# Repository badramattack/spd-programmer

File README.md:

# SPD programmer board

A small board to read, edit, program and restore the SPD EEPROM of **DDR4 and
DDR5 DIMMs** (UDIMM and RDIMM), built around a Raspberry Pi Pico (RP2040) and
half of a cut DDR5 DIMM socket. Edits can be made from a PC (`spdtool`) or
with no PC at all: insert a module, hold **Program**, and the board applies a
preset (by default a BadRAM-style extra row address bit) while keeping a
backup; **Restore** undoes it.

- DDR4 (EE1004 + TSE2004) and DDR5 (SPD5118 hub) on one half socket.
- Reversible write protection: DDR4 with the SA0 high voltage generated on the
  board, DDR5 through the hub's offline mode.
- Safety: rails are only on during an operation, after the mode switches and a
  seating check; current-limited supplies; watchdog.
- Decoding and editing of speed, timings, refresh, capacity and identity
  fields; CRCs and the serial number are updated automatically.
- Presets for the Program button are written in Python and uploaded over USB.

| Path | Contents |
|---|---|
| [`kicad/`](kicad/) | KiCad 10 project: schematic, PCB, project footprints (`spd-programmer.pretty`), JLCPCB BOM and placement files, Gerbers |
| [`firmware/`](firmware/) | Pico SDK firmware: USB command interface, buttons, presets ([README](firmware/README.md)) |
| [`host/`](host/) | `spdtool`, the Python host tool and library ([README](host/README.md)) |
| [`docs/`](docs/) | Reference documentation: [hardware](docs/hardware.md), [Program/Restore design and formats](docs/program-restore.md), [firmware internals](docs/firmware.md) |

## Using it

> [!CAUTION]
> **Set the mode switches to match the module type before inserting.** The
> board applies voltages based on the mode switches, which are not compatible
> across module types. A mode switch that does not match the inserted module
> type may damage that module.

1. Set the two mode switches (DDR4/DDR5, UDIMM/RDIMM) to match the module;
   two of the four mode LEDs show the selection.
2. Insert the module: The boad accepts both DDR4 and DDR5 modules, but **DDR4 modules must be rotated 180°**. Insert DDR5 modules with pin 1 at the end of the socket, and insert DDR4 modules with pin 288 at the end of the socket. The pin numbering is usually printed on the module near the pins. Push fully against the end of the socket. If the board raises alignment fault (single blink), recheck pin alignment.
3. From a PC: `pip install ./host`, then `spdtool info`. Without a PC: hold
   Program (the button labelled **BadRAM** on the board) for 1 s to apply the
   active preset (by default `badram-row`), or press **Restore** to undo it.

| LED | Meaning |
|---|---|
| Busy | The module is powered: **do not remove it** |
| Done | The last operation succeeded |
| Modified (labelled BadRAM) | The module carries a Program change (Restore undoes it) |
| Fault | The last button press failed (see below) |
| HV | The DDR4 write-protect voltage is on (only during a DDR4 write-protect change) |
| DDR4 / DDR5 / UDIMM / RDIMM | The mode switch positions |

After a failed button press, Fault stays lit and goes dark briefly **N times**
every few seconds, until the next press:

| N | Problem | What to check |
|---|---|---|
| 1 | Insertion | a mode switch between positions; module not inserted, not fully seated, or offset by a pin |
| 2 | Electrical | no answer from the module (I2C), supply too low, over-current: reseat it, check the contacts |
| 3 | Wrong module | the module type doesn't match the switches, or the active preset has nothing for this generation |
| 4 | Refused | already modified (Restore first), nothing to restore, the preset doesn't apply (e.g. already at the maximum), or the module changed since Program |
| 5 | Write failed | write protection couldn't be cleared, or the read-back didn't match |

`spdtool button` shows the exact reason for the last press.

See [`host/README.md`](host/README.md) for everything `spdtool` does, and how
to write your own presets.

## How it works

A summary; [`docs/hardware.md`](docs/hardware.md) has the details and the
reasoning behind each block.

**One socket for both generations.** The board uses contacts 1–69 and
145–213 of a DDR5 socket cut in half. A DDR4 module rotated by 180° puts its
SPD pins on the same few contacts, so one footprint serves both. Only these
contacts are connected:

| Contact | DDR4 (rotated) | DDR5 UDIMM | DDR5 RDIMM | Board |
|---|---|---|---|---|
| 1 | VPP | VIN_BULK | VIN_BULK | 5 V, switched, current-limited (DDR5 UDIMM only) |
| 3 | VPP | RFU | VIN_MGMT | 3.3 V, switched, current-limited (DDR5 RDIMM only) |
| 4 | SDA | HSCL | HSCL | I2C |
| 5 | VDDSPD | HSDA | HSDA | DDR4: 2.5 V supply (switched, 47 Ω); DDR5: I2C data |
| 6 | VSS | VSS | VSS | GND |
| 8 | VSS | VSS | VSS | seating check |
| 148 | SCL | HSA | HSA | DDR4: I2C clock; DDR5: grounded by a FET |
| 149, 51 | SA1, SA2 | RFU, CB0_A | RFU, CB0_A | 10 k to GND |
| 150 | SA0 | VSS | RFU | 10 k to GND; 8.5 V for DDR4 write-protect commands |
| 151 | VSS | PWR_EN | VSS | 10 k to GND (keeps the DDR5 UDIMM PMIC regulators off) |

**Power.** Everything comes from the Pico's USB. Each mode enables only its own
supplies, and only during an operation: a DDR5 UDIMM gets 5 V on VIN_BULK, a
DDR5 RDIMM 3.3 V on VIN_MGMT (both behind TPS2553 current-limit switches); the
PMIC's own LDO then powers the SPD hub, while its main regulators stay off. A
DDR4 module gets 2.5 V on VDDSPD. The I2C pull-ups go to a switched 2.5 V rail,
which suits the DDR4 RDIMM register's 2.5 V I2C as well as the other modules.

**Write protection.** DDR5: HSA is grounded before the hub is powered, which
starts it in offline mode, where the block protection can be cleared. DDR4:
the reversible write-protect commands need 7–10 V on SA0 (contact 150); a
charge-pump doubler and an 8.5 V LDO generate it, only for the duration of the
command and only in DDR4 mode.

**Seating check.** Contact 8 is VSS on every module type. Before any rail is
enabled the firmware measures it with a short pull-up pulse: VSS means
seated; a module offset by one pin puts a data or unused pad there instead,
and the board refuses to power it. The firmware also checks that the SPD type
bytes match the mode switches before it writes anything.

## Building one

- **PCB and assembly:** `kicad/` contains the Gerbers and the JLCPCB BOM and
  placement files; all parts except the Pico and the socket can be assembled by
  JLCPCB.
- **Pico:** a Raspberry Pi Pico (RP2040), soldered by its castellations.
- **Socket:** an Amphenol DDR504112805K (288-pin DDR5, vertical SMT), cut at
  the key; one socket gives two boards. The board uses positions 1–69 counted
  from the end tower; remove the key bump on the half that has it. Solder it
  by hand: hot air without bottom heating melts the housing.
- **Firmware:** build and flash as in [`firmware/README.md`](firmware/README.md).
- **Check:** with an empty socket, `spdtool status` and `spdtool debug` let you
  measure each mode's supplies before inserting a module (`host/README.md`,
  "Debugging and bring-up").

## Status

The first boards are built and tested with DDR5 RDIMMs (one with an XMP 3.0
profile) and a DDR4 RDIMM: reading, writing, write protection (DDR4 with the
high voltage), seating detection, the buttons and Program/Restore with every
built-in preset. DDR5 UDIMMs are not tested yet.

## Caution

Changing the SPD of a module changes how a system configures it; a wrong value
can keep a machine from booting. `spdtool` and the Program button keep backups
of what they change, but keep your own copy (`spdtool dump`) before editing a
module you care about.

## License

MIT (see [`LICENSE`](LICENSE)), for the hardware design files in `kicad/` as
well as the firmware and the host tool.

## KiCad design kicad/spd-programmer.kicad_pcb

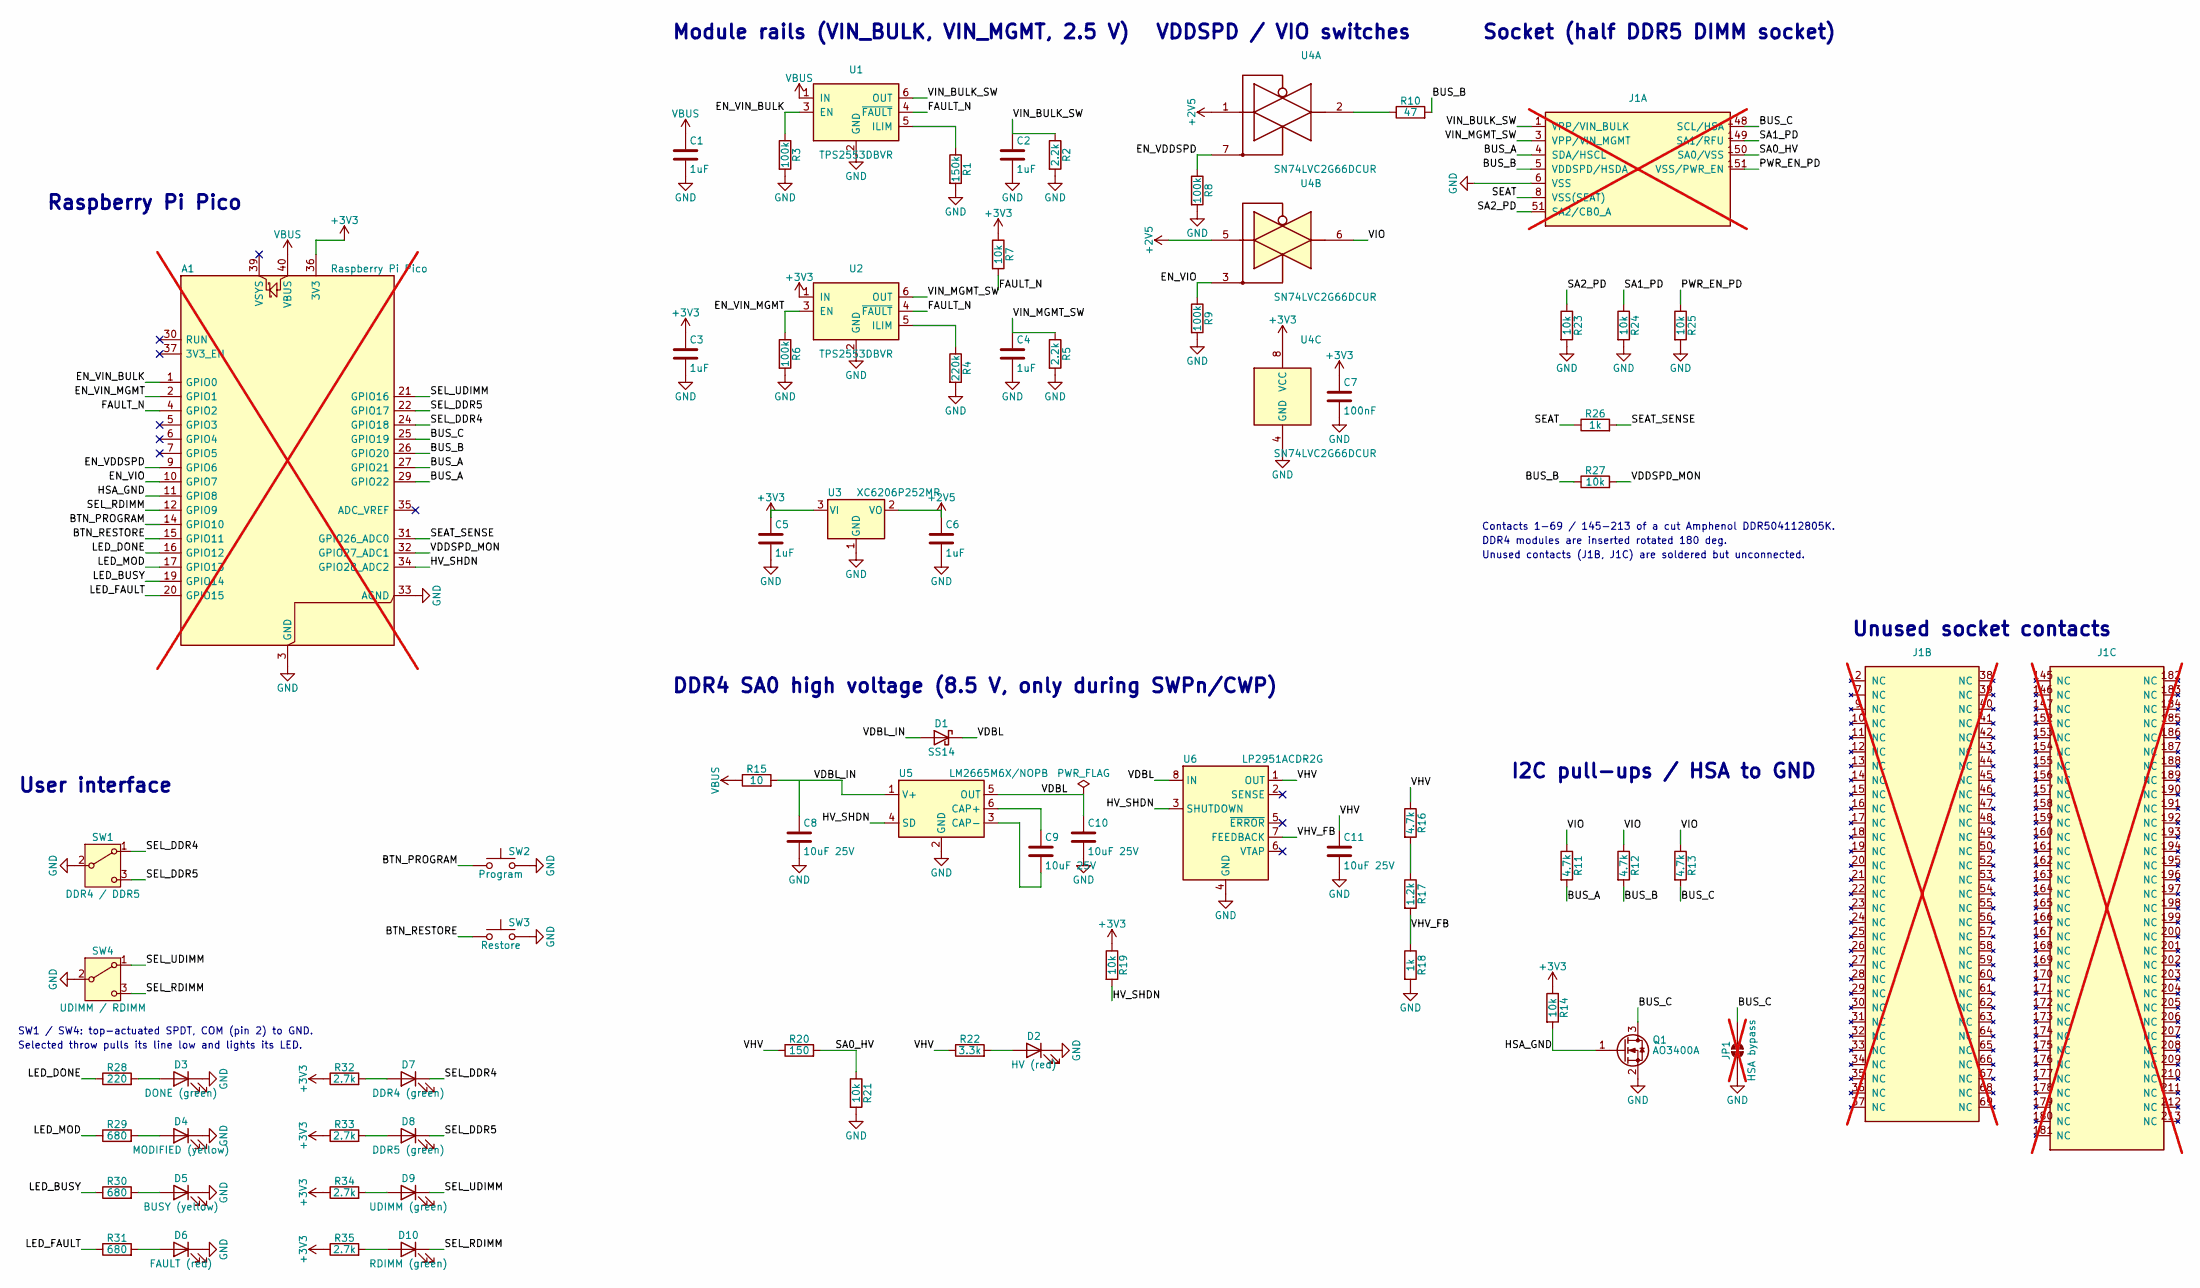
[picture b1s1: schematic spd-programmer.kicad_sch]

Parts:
A1: Raspberry Pi Pico; RaspberryPi_Pico_SMD_HandSolder; MPN Raspberry Pi Pico (RP2040); not fitted
C1, C2, C3, C4, C5, C6: 1uF; C_0603_1608Metric; MPN 1uF X5R 0603; LCSC C15849
C7: 100nF; C_0603_1608Metric; MPN 100nF X7R 0603; LCSC C14663
C8, C9, C10, C11: 10uF 25V; C_0805_2012Metric; MPN 10uF 25V X5R 0805; LCSC C15850
D1: SS14; D_SMA; MPN SS14 (MDD); Farnell_MPN SS14 (Multicomp Pro)
D2: HV (red); LED_0805_2012Metric; MPN NCD0805R1; Farnell_MPN TBD (0805 red)
D3: DONE (green); LED_0805_2012Metric; MPN KT-0805G; Farnell_MPN MP008291
D4: MODIFIED (yellow); LED_0805_2012Metric; MPN KT-0805Y; Farnell_MPN TBD (0805 yellow)
D5: BUSY (yellow); LED_0805_2012Metric; MPN KT-0805Y; Farnell_MPN TBD (0805 yellow)
D6: FAULT (red); LED_0805_2012Metric; MPN NCD0805R1; Farnell_MPN TBD (0805 red)
D7: DDR4 (green); LED_0805_2012Metric; MPN KT-0805G; Farnell_MPN MP008291
D8: DDR5 (green); LED_0805_2012Metric; MPN KT-0805G; Farnell_MPN MP008291
D9: UDIMM (green); LED_0805_2012Metric; MPN KT-0805G; Farnell_MPN MP008291
D10: RDIMM (green); LED_0805_2012Metric; MPN KT-0805G; Farnell_MPN MP008291
J1: DDR504112805K_half; DDR5_DIMM_HalfSocket_P0.85mm; MPN Amphenol DDR504112805K (half); not fitted
JP1: HSA bypass; SolderJumper-2_P1.3mm_Open_TrianglePad1.0x1.5mm; MPN Solder jumper; not fitted
Q1: AO3400A; SOT-23; MPN AO3400A; Farnell_MPN XP2344GN
R1: 150k; R_0603_1608Metric; MPN 150k 1% 0603; LCSC C22807
R2, R5: 2.2k; R_0603_1608Metric; MPN 2.2k 1% 0603; LCSC C4190
R3, R6, R8, R9: 100k; R_0603_1608Metric; MPN 100k 1% 0603; LCSC C25803
R4: 220k; R_0603_1608Metric; MPN 220k 1% 0603; LCSC C22961
R7, R14, R19, R21, R23, R24, R25, R27: 10k; R_0603_1608Metric; MPN 10k 1% 0603; LCSC C25804
R10: 47; R_0805_2012Metric; MPN 47 1% 0805; LCSC C17714
R11, R12, R13, R16: 4.7k; R_0603_1608Metric; MPN 4.7k 1% 0603; LCSC C23162
R15: 10; R_0603_1608Metric; MPN 10 1% 0603; LCSC C22859
R17: 1.2k; R_0603_1608Metric; MPN 1.2k 1% 0603; LCSC C22765
R18, R26: 1k; R_0603_1608Metric; MPN 1k 1% 0603; LCSC C21190
R20: 150; R_0603_1608Metric; MPN 150 1% 0603; LCSC C22808
R22: 3.3k; R_0603_1608Metric; MPN 3.3k 1% 0603; LCSC C22978
R28: 220; R_0603_1608Metric; MPN 220 1% 0603; LCSC C22962
R29, R30, R31: 680; R_0603_1608Metric; MPN 680 1% 0603; LCSC C23228
R32, R33, R34, R35: 2.7k; R_0603_1608Metric; MPN 2.7k 1% 0603; LCSC C13167
SW1: DDR4 / DDR5; SW_SPDT_CK_JS102011SAQN_SCQN_ShouHan_MST-22D18G2; MPN SHOU HAN MST-22D18G2-3J; LCSC C2875122
SW2: Program; SW_Push_1P1T_XKB_TS-1187A; MPN TS-1187A-B-A-B; Farnell_MPN TM-533I-Q-T/R
SW3: Restore; SW_Push_1P1T_XKB_TS-1187A; MPN TS-1187A-B-A-B; Farnell_MPN TM-533I-Q-T/R
SW4: UDIMM / RDIMM; SW_SPDT_CK_JS102011SAQN_SCQN_ShouHan_MST-22D18G2; MPN SHOU HAN MST-22D18G2-3J; LCSC C2875122
U1, U2: TPS2553DBVR; SOT-23-6; MPN TPS2553DBVR; LCSC C55266
U3: XC6206P252MR; SOT-23-3; MPN XC6206P252MR; Farnell_MPN MCP1700T-2502E/TT
U4: SN74LVC2G66DCUR; VSSOP-8_2.3x2mm_P0.5mm; MPN SN74LVC2G66DCUR; Farnell_MPN 74LVC2G66DC,125
U5: LM2665M6X/NOPB; SOT-23-6; MPN LM2665M6X/NOPB; Farnell_MPN LM2665M6/NOPB
U6: LP2951ACDR2G; SOIC-8_3.9x4.9mm_P1.27mm; MPN LP2951ACDR2G; Farnell_MPN NCV2951ACDR2G

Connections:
+2V5: C6.1, U3.2 (VO), U4.1, U4.5
+3V3: A1.36 (3V3), C3.1, C5.1, C7.1, R7.1, R14.1, R19.1, R32.1, R33.1, R34.1, R35.1, U2.1 (IN), U3.3 (VI), U4.8 (VCC)
/BTN_PROGRAM: A1.14 (GPIO10), SW2.1
/BTN_RESTORE: A1.15 (GPIO11), SW3.1
/BUS_A: A1.27 (GPIO21), A1.29 (GPIO22), J1.4 (SDA/HSCL), R11.2
/BUS_B: A1.26 (GPIO20), J1.5 (VDDSPD/HSDA), R10.2, R12.2, R27.1
/BUS_C: A1.25 (GPIO19), J1.148 (SCL/HSA), JP1.2 (B), Q1.3 (D), R13.2
/EN_VDDSPD: A1.9 (GPIO6), R8.1, U4.7
/EN_VIN_BULK: A1.1 (GPIO0), R3.1, U1.3 (EN)
/EN_VIN_MGMT: A1.2 (GPIO1), R6.1, U2.3 (EN)
/EN_VIO: A1.10 (GPIO7), R9.1, U4.3
/FAULT_N: A1.4 (GPIO2), R7.2, U1.4 (~FAULT), U2.4 (~FAULT)
/HSA_GND: A1.11 (GPIO8), Q1.1 (G), R14.2
/HV_SHDN: A1.34 (GPIO28_ADC2), R19.2, U5.4 (SD), U6.3 (SHUTDOWN)
/LED_BUSY: A1.19 (GPIO14), R30.1
/LED_DONE: A1.16 (GPIO12), R28.1
/LED_FAULT: A1.20 (GPIO15), R31.1
/LED_MOD: A1.17 (GPIO13), R29.1
/PWR_EN_PD: J1.151 (VSS/PWR_EN), R25.1
/SA0_HV: J1.150 (SA0/VSS), R20.2, R21.1
/SA1_PD: J1.149 (SA1/RFU), R24.1
/SA2_PD: J1.51 (SA2/CB0_A), R23.1
/SEAT: J1.8 (VSS(SEAT)), R26.1
/SEAT_SENSE: A1.31 (GPIO26_ADC0), R26.2
/SEL_DDR4: A1.24 (GPIO18), D7.1 (K), SW1.1 (A)
/SEL_DDR5: A1.22 (GPIO17), D8.1 (K), SW1.3 (C)
/SEL_RDIMM: A1.12 (GPIO9), D10.1 (K), SW4.3 (C)
/SEL_UDIMM: A1.21 (GPIO16), D9.1 (K), SW4.1 (A)
/VDBL: C10.1, D1.1 (K), U5.5 (OUT), U6.8 (IN)
/VDBL_IN: C8.1, D1.2 (A), R15.2, U5.1 (V+)
/VDDSPD_MON: A1.32 (GPIO27_ADC1), R27.2
/VHV: C11.1, R16.1, R20.1, R22.1, U6.1 (OUT)
/VHV_FB: R17.2, R18.1, U6.7 (FEEDBACK)
/VIN_BULK_SW: C2.1, J1.1 (VPP/VIN_BULK), R2.1, U1.6 (OUT)
/VIN_MGMT_SW: C4.1, J1.3 (VPP/VIN_MGMT), R5.1, U2.6 (OUT)
/VIO: R11.1, R12.1, R13.1, U4.6
GND: A1.3 (GND), A1.8 (GND), A1.13 (GND), A1.18 (GND), A1.23 (GND), A1.28 (GND), A1.33 (AGND), A1.38 (GND), C1.2, C2.2, C3.2, C4.2, C5.2, C6.2, C7.2, C8.2, C10.2, C11.2, D2.1 (K), D3.1 (K), D4.1 (K), D5.1 (K), D6.1 (K), J1.6 (VSS), JP1.1 (A), Q1.2 (S), R1.2, R2.2, R3.2, R4.2, R5.2, R6.2, R8.2, R9.2, R18.2, R21.2, R23.2, R24.2, R25.2, SW1.2 (B), SW2.2, SW3.2, SW4.2 (B), U1.2 (GND), U2.2 (GND), U3.1 (GND), U4.4 (GND), U5.2 (GND), U6.4 (GND)
unnamed: D2.2 (A), R22.2
unnamed: D3.2 (A), R28.2
unnamed: D4.2 (A), R29.2
unnamed: D5.2 (A), R30.2
unnamed: D6.2 (A), R31.2
unnamed: D7.2 (A), R32.2
unnamed: D8.2 (A), R33.2
unnamed: D9.2 (A), R34.2
unnamed: D10.2 (A), R35.2
unnamed: R10.1, U4.2
unnamed: R16.2, R17.1
unnamed: R1.1, U1.5 (ILIM)
unnamed: R4.1, U2.5 (ILIM)
unnamed: C9.1, U5.6 (CAP+)
unnamed: C9.2, U5.3 (CAP-)
VBUS: A1.40 (VBUS), C1.1, R15.1, U1.1 (IN)

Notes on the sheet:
User interface
DDR4 SA0 high voltage (8.5 V, only during SWPn/CWP)
Unused socket contacts
SW1 / SW4: top-actuated SPDT, COM (pin 2) to GND.
Unused contacts (J1B, J1C) are soldered but unconnected.
Module rails (VIN_BULK, VIN_MGMT, 2.5 V)
Socket (half DDR5 DIMM socket)
VDDSPD / VIO switches
I2C pull-ups / HSA to GND
Raspberry Pi Pico
DDR4 modules are inserted rotated 180 deg.
Selected throw pulls its line low and lights its LED.
Contacts 1-69 / 145-213 of a cut Amphenol DDR504112805K.

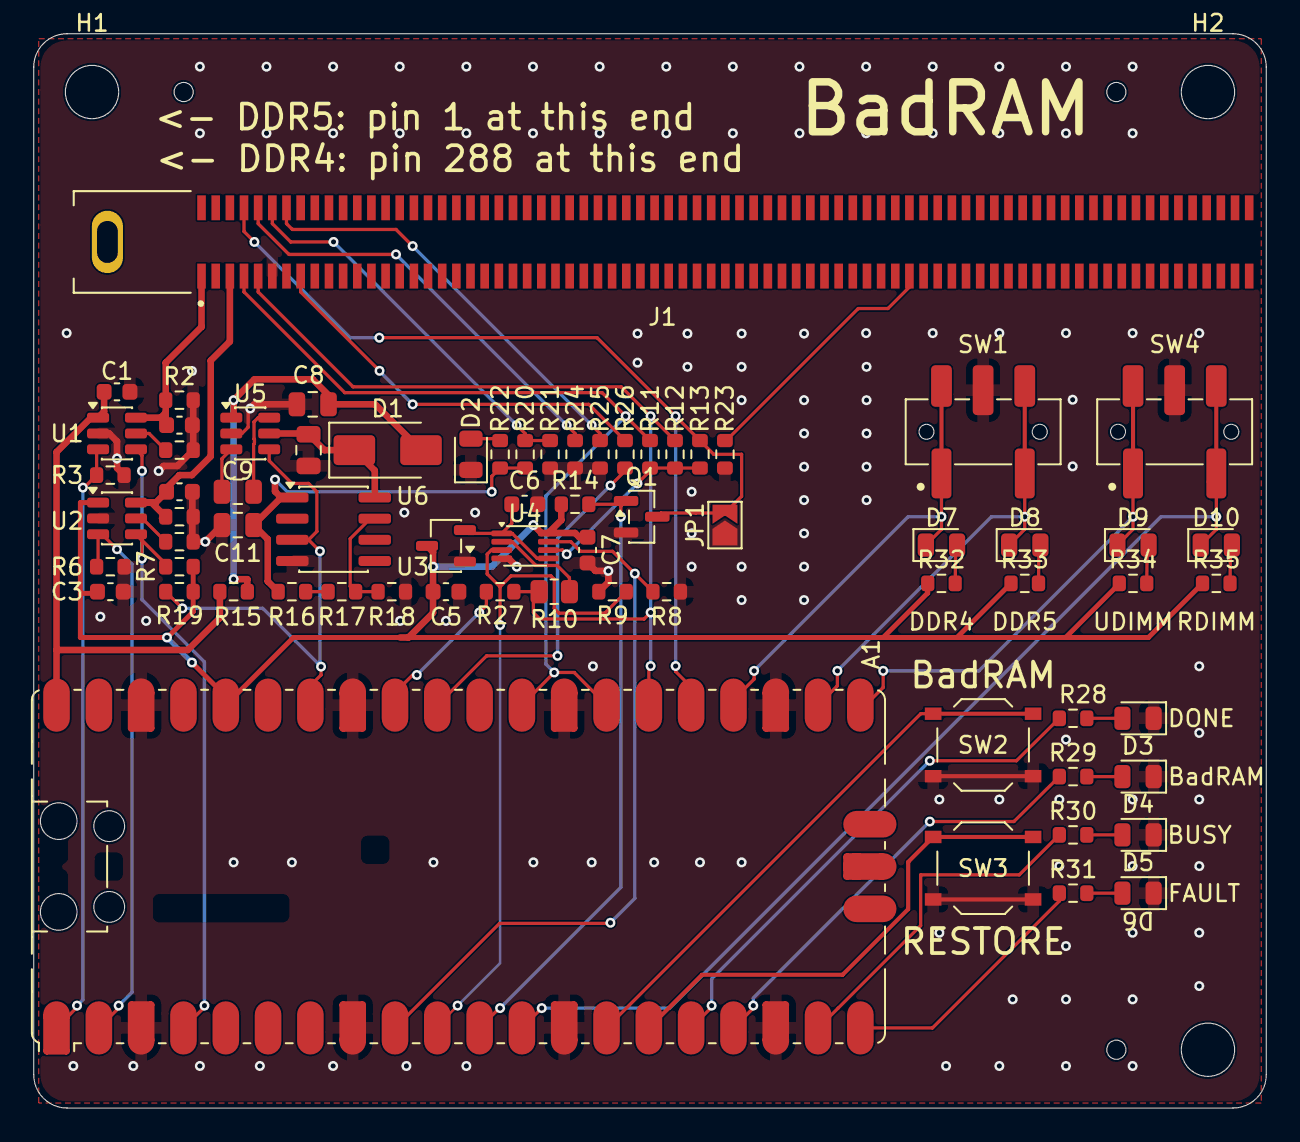
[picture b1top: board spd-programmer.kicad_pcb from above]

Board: 2 copper layers, 74.0 x 64.5 mm, 74 parts (1 on the bottom side), 53 nets.

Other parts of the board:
H1, H2, H3: MountingHole_3.2mm_M3
LOGO1: Logos

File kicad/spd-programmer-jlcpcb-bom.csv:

"Comment","Designator","Footprint","JLCPCB Part #"
"1uF","C1,C2,C3,C4,C5,C6","Capacitor_SMD:C_0603_1608Metric","C15849"
"100nF","C7","Capacitor_SMD:C_0603_1608Metric","C14663"
"10uF 25V","C8,C9,C10,C11","Capacitor_SMD:C_0805_2012Metric","C15850"
"SS14","D1","Diode_SMD:D_SMA","C2480"
"Red LED 0805","D2,D6","LED_SMD:LED_0805_2012Metric","C84256"
"Green LED 0805","D3,D7,D8,D9,D10","LED_SMD:LED_0805_2012Metric","C2297"
"Yellow LED 0805","D4,D5","LED_SMD:LED_0805_2012Metric","C2296"
"AO3400A","Q1","Package_TO_SOT_SMD:SOT-23","C20917"
"150k","R1","Resistor_SMD:R_0603_1608Metric","C22807"
"2.2k","R2,R5","Resistor_SMD:R_0603_1608Metric","C4190"
"100k","R3,R6,R8,R9","Resistor_SMD:R_0603_1608Metric","C25803"
"220k","R4","Resistor_SMD:R_0603_1608Metric","C22961"
"10k","R7,R14,R19,R21,R23,R24,R25,R27","Resistor_SMD:R_0603_1608Metric","C25804"
"47","R10","Resistor_SMD:R_0805_2012Metric","C17714"
"4.7k","R11,R12,R13,R16","Resistor_SMD:R_0603_1608Metric","C23162"
"10","R15","Resistor_SMD:R_0603_1608Metric","C22859"
"1.2k","R17","Resistor_SMD:R_0603_1608Metric","C22765"
"1k","R18,R26","Resistor_SMD:R_0603_1608Metric","C21190"
"150","R20","Resistor_SMD:R_0603_1608Metric","C22808"
"3.3k","R22","Resistor_SMD:R_0603_1608Metric","C22978"
"220","R28","Resistor_SMD:R_0603_1608Metric","C22962"
"2.7k","R32,R33,R34,R35","Resistor_SMD:R_0603_1608Metric","C13167"
"680","R29,R30,R31","Resistor_SMD:R_0603_1608Metric","C23228"
"MST-22D18G2-3J SPDT slide switch","SW1,SW4","spd:SW_SPDT_CK_JS102011SAQN_SCQN_ShouHan_MST-22D18G2","C2875122"
"TS-1187A tactile switch","SW2,SW3","Button_Switch_SMD:SW_Push_1P1T_XKB_TS-1187A","C318884"
"TPS2553DBVR","U1,U2","Package_TO_SOT_SMD:SOT-23-6","C55266"
"XC6206P252MR","U3","Package_TO_SOT_SMD:SOT-23-3","C15906"
"SN74LVC2G66DCUR","U4","Package_SO:VSSOP-8_2.3x2mm_P0.5mm","C181970"
"LM2665M6X/NOPB","U5","Package_TO_SOT_SMD:SOT-23-6","C201725"
"LP2951ACDR2G","U6","Package_SO:SOIC-8_3.9x4.9mm_P1.27mm","C232432"

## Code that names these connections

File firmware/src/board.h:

// Pin map and electrical constants of the SPD programmer board.
// Source of truth: the KiCad schematic (kicad/spd-programmer.kicad_sch).
#pragma once

#include "pico/stdlib.h"

#define FW_VERSION "0.1.0"
#define PROTO_VERSION 1

// Module supply switches (all have 100 k pull-downs: off by default).
#define PIN_EN_VIN_BULK 0   // U1 TPS2553, 5 V, DDR5 UDIMM only (contact 1)
#define PIN_EN_VIN_MGMT 1   // U2 TPS2553, 3.3 V, DDR5 RDIMM only (contact 3)
#define PIN_FAULT_N     2   // U1/U2 FAULT, wire-OR, 10 k pull-up
#define PIN_EN_VDDSPD   6   // U4 switch 1, 2.5 V to contact 5, DDR4 only
#define PIN_EN_VIO      7   // U4 switch 2, 2.5 V I2C pull-up rail
#define PIN_HSA_GND     8   // Q4 gate, 100 k pull-up: high = contact 148 grounded
#define PIN_HV_SHDN     28  // U5 SD + U6 SHUTDOWN, 10 k pull-up: high = VHV off

// User interface. Select lines are low when that position is selected.
#define PIN_SEL_RDIMM   9
#define PIN_SEL_UDIMM   16
#define PIN_SEL_DDR5    17
#define PIN_SEL_DDR4    18
#define PIN_BTN_PROGRAM 10
#define PIN_BTN_RESTORE 11
#define PIN_LED_DONE    12
#define PIN_LED_MOD     13
#define PIN_LED_BUSY    14
#define PIN_LED_FAULT   15  // the four LEDs must stay consecutive (board.c)

// LED brightness, PWM duty in 1/LED_LEVEL_MAX. The green Done LED is much
// brighter than the yellow and red ones at the same current.
#define LED_LEVEL_MAX   1000
#define LED_DONE_LEVEL  100   // matched by eye to the yellow and red LEDs (spdtool ledtune)
#define LED_MOD_LEVEL   1000
#define LED_BUSY_LEVEL  1000
#define LED_FAULT_LEVEL 1000

// I2C. Contact 4 is wired to both GP21 (I2C0 SCL) and GP22 (I2C1 SDA).
#define PIN_BUS_C       19  // contact 148: DDR4 SCL (I2C1) / DDR5 HSA
#define PIN_BUS_B       20  // contact 5:   DDR5 HSDA (I2C0 SDA) / DDR4 VDDSPD
#define PIN_BUS_A_I2C0  21  // contact 4:   DDR5 HSCL (I2C0 SCL)
#define PIN_BUS_A_I2C1  22  // contact 4:   DDR4 SDA (I2C1 SDA)

// ADC inputs.
#define PIN_SEAT_SENSE  26  // ADC0, contact 8 through 1 k
#define PIN_VDDSPD_MON  27  // ADC1, contact 5 through 10 k
#define ADC_CH_SEAT     0
#define ADC_CH_VDDSPD   1

// Seating check. Contact 8 is VSS on every DDR4 and DDR5 module type; a module
// offset by one pin puts a DQ or RFU pad there instead. The internal pull-up
// (50-80 k), pulsed for 1 ms so the module's supplies barely charge, against
// contact 8 = VSS through 1 k gives about 40-65 mV; a DQ pin clamped by its
// ESD diode reads 0.3-0.5 V; an open contact reads about 3.3 V.
#define SEAT_PULSE_US        1000
#define SEAT_SEATED_MAX_MV   200
#define SEAT_EMPTY_MIN_MV    2500

// DDR4 VDDSPD at contact 5 must be at least this before the first access.
#define VDDSPD_MIN_MV        2250

// Timing.
#define T_DISCHARGE_MS       500   // rails off -> next power-up
#define T_VDDSPD_SETTLE_MS   5
#define T_DDR5_POR_MS        50    // VIN on -> PMIC LDO + hub POR
#define T_HV_SETTLE_MS       50    // VHV on -> doubler + LDO settled
#define T_HV_OFF_MS          100   // VHV off -> normal SPD access
#define DEBUG_IDLE_S         300   // debug mode: rails off after this long without a command
#define DEBUG_HV_IDLE_S      60    // debug mode with VHV

#define I2C_BAUD             100000

void board_init(void);
void led_set(uint pin, bool on);
bool led_get(uint pin);
void led_set_level(uint pin, uint level);
uint led_level(uint pin);
uint32_t adc_read_mv(uint channel);
